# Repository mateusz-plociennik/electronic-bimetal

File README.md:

# electronic-bimetal

## English
### Description
The system was designed to replace the former used bimetal to temporarily stop the train on an isolated track.

### Programming polarization and timings:
1. Make sure that there is no drive on the insulated track.
2. Press the programming button for approx. 5 seconds, i.e. until the programming LED shines with a stronger light. The polarity of the system is memorized at this time.
3. Insert the drive into the insulated track (preferably to drive in automatically). From that moment, the detention time begins to count.
4. Press the programming button so that the train leaves the insulated path. When the programming button is pressed, the parking time is memorized, while at the moment of releasing the button - driving time.
5. End of programming. The system goes into normal mode.

## Polski
### Opis
Układ został zaprojektowany by zastąpić bimetal używany dawnej do tymczasowego zatrzymywania pociągu na izolowanym torze.

### Programowanie polaryzacji i czasów:
1. Upewnij się, że na izolowanym torze nie ma napędu.
2. Wciśnij przycisk programowania przez ok. 5 sekund, tj. tak długo, aż dioda programowania będzie świeciła mocniejszym światłem. W tym momencie zostaje zapamiętana polaryzacja układu.
3. Wprowadź napęd na izolowany tor (najlepiej, żeby wjechał samoczynnie). Od tego momentu zaczyna się naliczanie czasu zatrzymania.
4. Wciśnij przycisk programowania tak długo, by pociąg zjechał z izolowanego toru. W momencie wciśnięcia przycisku programowania następuje zapamiętanie czasu postoju, natomiast w momencie puszczenia przycisku - czasu jazdy.
5. Koniec programowania. Układ przechodzi w tryb normalny.

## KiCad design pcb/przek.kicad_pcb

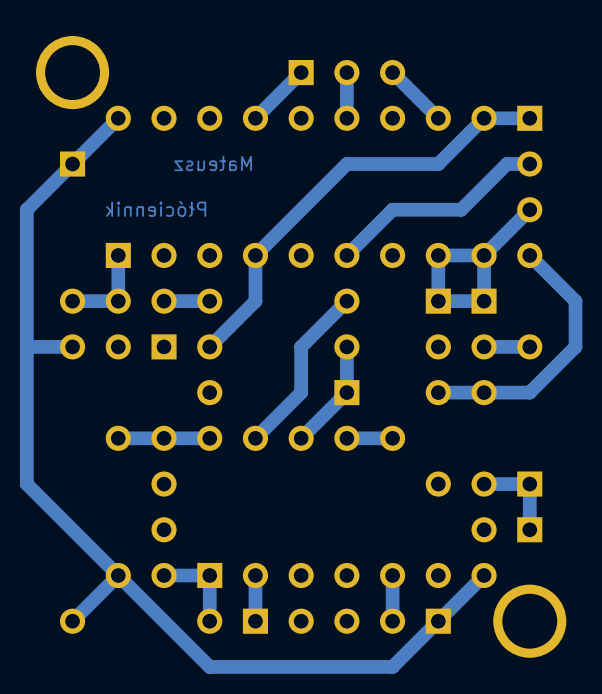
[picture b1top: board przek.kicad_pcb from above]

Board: 2 copper layers, 26 parts (0 on the bottom side), 20 nets.

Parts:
C1, C3, C4, C5: 100n; C1
C2: 2u2; C1V5
D1, D4: 1N5817; D3
D2: LED; LED-3MM
D3: 3V3; D3
IC1: ATTINY13-P; DIP-8__300
J1, J2: CONN_3; SIL-3
K1: HFD27/003; DIP-16__300
L1: 10u; R3
M1, M2: P***; 1pin
P1: CONN_4; SIL-4
P2: CONN_3; SIL-3
Q1: BC547B; TO92
R1, R3, R4: 330; R3
R2: 4k7; R3
R5: 4K7; R3
SW1: SW_PUSH; SIL-2
U1: L4931; LM78XX-TO92

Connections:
+5V: C2.1, C5.1, D4.2, K1.16, L1.1, R2.1, U1.VO
GND: C1.2, C2.2, C3.2, C4.2, C5.2, D2.2, D3.1, IC1.4, J2.2, Q1.1, SW1.2, U1.GND
unnamed: D2.1, R1.1
unnamed: IC1.2, SW1.1
unnamed: D1.1, J1.2
unnamed: D4.1, K1.1, Q1.3
unnamed: K1.11, P2.2
unnamed: K1.6, P1.2
unnamed: K1.13, P2.1
unnamed: K1.9, P2.3
unnamed: C1.1, D1.2, U1.VI
unnamed: Q1.2, R5.1
unnamed: IC1.5, R1.2
unnamed: C3.1, IC1.8, L1.2
unnamed: C4.1, IC1.1, R2.2
RELAY: IC1.7, R5.2
TOR_S: K1.4, P1.1, R3.2, R4.1
TOR_Z1: J1.1, J2.1, K1.8, P1.3, R3.1
TOR_Z2: J1.3, J2.3, P1.4
TRIG: D3.2, IC1.6, R4.2

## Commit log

2018-09-02 Add pcb & src directories
